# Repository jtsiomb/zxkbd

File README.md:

ZX Spectrum PS/2 keyboard controller
====================================

About
-----
This project is an PS/2 keyboard controller for the ZX Spectrum. It makes it
possible to connect and use an external PS/2 keyboard with the spectrum. It's
based on the a500kbd code: https://github.com/jtsiomb/a500kbd

The PS/2 keyboard controller is built around an AVR atmega168 microcontroller.
The firmware reads PS/2 keyboard scancodes, maintains a virtual spectrum
keyboard state, and monitors the address bus to keep the data lines going into
the ULA continuously up to date with the selected key row state.

NOTE: not done. check back soon.

License
-------
Copyright (C) 2020 John Tsiombikas <nuclear@member.fsf.org>

You are free to use, reproduce, modify, redistribute any parts of this project,
provided you make any derivative work you release, freely available under the
same terms.

More specifically the hardware design is released under the Creative Commons
Attribution Share-Alike license (see `LICENSE.hw` for details), and the
software/firmware is released under the GNU General Public License v3, or later
(see `LICENSE.fw` for details).

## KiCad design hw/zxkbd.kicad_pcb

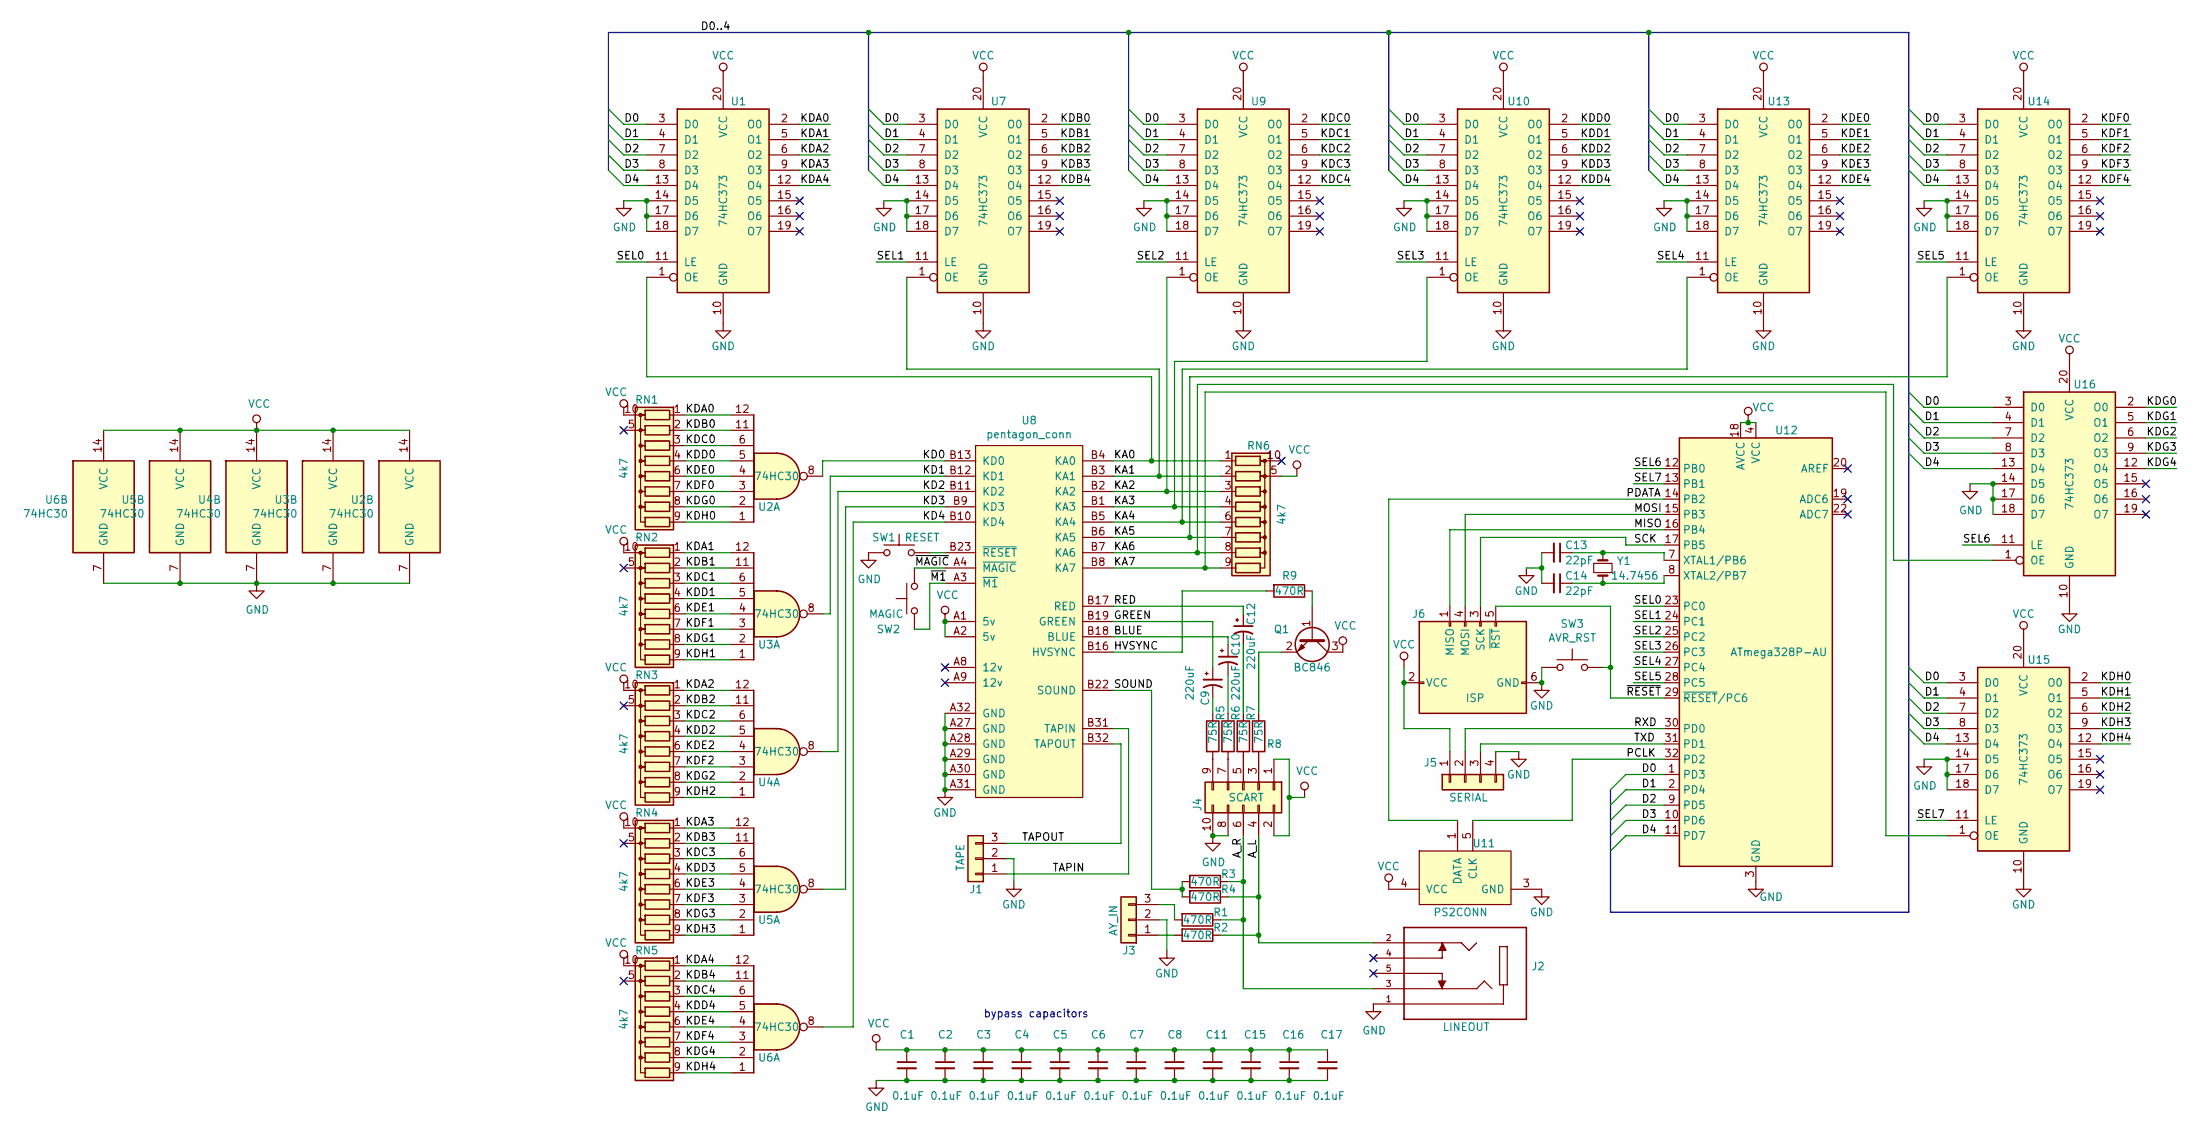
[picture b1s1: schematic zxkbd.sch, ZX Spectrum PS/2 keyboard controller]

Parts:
C1, C2, C3, C4, C5, C6, C7, C8, C11, C15, C16, C17: 0.1uF; C_0805_2012Metric_Pad1.15x1.40mm_HandSolder
C9, C10, C12: 220uF; CP_Elec_6.3x7.7
C13, C14: 22pF; C_0805_2012Metric_Pad1.15x1.40mm_HandSolder
J1: TAPE; PinHeader_1x03_P2.54mm_Vertical
J2: LINEOUT; cui_sj1-3525ng
J3: AY_IN; PinHeader_1x03_P2.54mm_Vertical
J4: SCART; IDC-Header_2x05_P2.54mm_Vertical
J5: SERIAL; PinHeader_1x04_P2.54mm_Vertical
J6: ISP; IDC-Header_2x03_P2.54mm_Vertical
Q1: BC846; SOT-23
R1, R2, R3, R4, R9: 470R; R_0805_2012Metric_Pad1.15x1.40mm_HandSolder
R5, R6, R7, R8: 75R; R_0805_2012Metric_Pad1.15x1.40mm_HandSolder
RN1, RN2, RN3, RN4, RN5, RN6: 4k7; R_Array_Convex_5x1206
SW1: RESET; SW_Push_1P1T_NO_6x6mm_H9.5mm
SW2: MAGIC; SW_Push_1P1T_NO_6x6mm_H9.5mm
SW3: AVR_RST; SW_Push_1P1T_NO_6x6mm_H9.5mm
U1, U7, U9, U10, U13, U14, U15, U16: 74HC373; SOIC-20W_7.5x12.8mm_P1.27mm
U2, U3, U4, U5, U6: 74HC30; SOIC-14_3.9x8.7mm_P1.27mm
U8: pentagon_conn; pentconn
U11: PS2CONN; ps2conn
U12: ATmega328P-AU; TQFP-32_7x7mm_P0.8mm
Y1: 14.7456; Crystal_SMD_ECS_CSM3X-2Pin_7.6x4.1mm

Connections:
/A_L: J2.2, J4.4, R2.1, R4.1
/A_R: J2.3, J4.6, R1.1, R3.1
/BLUE: C10.1, U8.B18 (BLUE)
/D0: U1.3 (D0), U7.3 (D0), U9.3 (D0), U10.3 (D0), U12.1 (PD3), U13.3 (D0), U14.3 (D0), U15.3 (D0), U16.3 (D0)
/D1: U1.4 (D1), U7.4 (D1), U9.4 (D1), U10.4 (D1), U12.2 (PD4), U13.4 (D1), U14.4 (D1), U15.4 (D1), U16.4 (D1)
/D2: U1.7 (D2), U7.7 (D2), U9.7 (D2), U10.7 (D2), U12.9 (PD5), U13.7 (D2), U14.7 (D2), U15.7 (D2), U16.7 (D2)
/D3: U1.8 (D3), U7.8 (D3), U9.8 (D3), U10.8 (D3), U12.10 (PD6), U13.8 (D3), U14.8 (D3), U15.8 (D3), U16.8 (D3)
/D4: U1.13 (D4), U7.13 (D4), U9.13 (D4), U10.13 (D4), U12.11 (PD7), U13.13 (D4), U14.13 (D4), U15.13 (D4), U16.13 (D4)
/GREEN: C9.1, U8.B19 (GREEN)
/HVSYNC: R9.2, U8.B16 (HVSYNC)
/KA0: RN6.1 (R1), U1.1 (OE), U8.B4 (KA0)
/KA1: RN6.2 (R2), U7.1 (OE), U8.B3 (KA1)
/KA2: RN6.3 (R3), U8.B2 (KA2), U9.1 (OE)
/KA3: RN6.4 (R4), U8.B1 (KA3), U10.1 (OE)
/KA4: RN6.6 (R6), U8.B5 (KA4), U13.1 (OE)
/KA5: RN6.7 (R7), U8.B6 (KA5), U14.1 (OE)
/KA6: RN6.8 (R8), U8.B7 (KA6), U16.1 (OE)
/KA7: RN6.9 (R9), U8.B8 (KA7), U15.1 (OE)
/KD0: U2.8, U8.B13 (KD0)
/KD1: U3.8, U8.B12 (KD1)
/KD2: U4.8, U8.B11 (KD2)
/KD3: U5.8, U8.B9 (KD3)
/KD4: U6.8, U8.B10 (KD4)
/KDA0: RN1.1 (R1), U1.2 (O0), U2.12
/KDA1: RN2.1 (R1), U1.5 (O1), U3.12
/KDA2: RN3.1 (R1), U1.6 (O2), U4.12
/KDA3: RN4.1 (R1), U1.9 (O3), U5.12
/KDA4: RN5.1 (R1), U1.12 (O4), U6.12
/KDB0: RN1.2 (R2), U2.11, U7.2 (O0)
/KDB1: RN2.2 (R2), U3.11, U7.5 (O1)
/KDB2: RN3.2 (R2), U4.11, U7.6 (O2)
/KDB3: RN4.2 (R2), U5.11, U7.9 (O3)
/KDB4: RN5.2 (R2), U6.11, U7.12 (O4)
/KDC0: RN1.3 (R3), U2.6, U9.2 (O0)
/KDC1: RN2.3 (R3), U3.6, U9.5 (O1)
/KDC2: RN3.3 (R3), U4.6, U9.6 (O2)
/KDC3: RN4.3 (R3), U5.6, U9.9 (O3)
/KDC4: RN5.3 (R3), U6.6, U9.12 (O4)
/KDD0: RN1.4 (R4), U2.5, U10.2 (O0)
/KDD1: RN2.4 (R4), U3.5, U10.5 (O1)
/KDD2: RN3.4 (R4), U4.5, U10.6 (O2)
/KDD3: RN4.4 (R4), U5.5, U10.9 (O3)
/KDD4: RN5.4 (R4), U6.5, U10.12 (O4)
/KDE0: RN1.6 (R6), U2.4, U13.2 (O0)
/KDE1: RN2.6 (R6), U3.4, U13.5 (O1)
/KDE2: RN3.6 (R6), U4.4, U13.6 (O2)
/KDE3: RN4.6 (R6), U5.4, U13.9 (O3)
/KDE4: RN5.6 (R6), U6.4, U13.12 (O4)
/KDF0: RN1.7 (R7), U2.3, U14.2 (O0)
/KDF1: RN2.7 (R7), U3.3, U14.5 (O1)
/KDF2: RN3.7 (R7), U4.3, U14.6 (O2)
/KDF3: RN4.7 (R7), U5.3, U14.9 (O3)
/KDF4: RN5.7 (R7), U6.3, U14.12 (O4)
/KDG0: RN1.8 (R8), U2.2, U16.2 (O0)
/KDG1: RN2.8 (R8), U3.2, U16.5 (O1)
/KDG2: RN3.8 (R8), U4.2, U16.6 (O2)
/KDG3: RN4.8 (R8), U5.2, U16.9 (O3)
/KDG4: RN5.8 (R8), U6.2, U16.12 (O4)
/KDH0: RN1.9 (R9), U2.1, U15.2 (O0)
/KDH1: RN2.9 (R9), U3.1, U15.5 (O1)
/KDH2: RN3.9 (R9), U4.1, U15.6 (O2)
/KDH3: RN4.9 (R9), U5.1, U15.9 (O3)
/KDH4: RN5.9 (R9), U6.1, U15.12 (O4)
/MISO: J6.1 (MISO), U12.16 (PB4)
/MOSI: J6.4 (MOSI), U12.15 (PB3)
/PCLK: U11.5 (CLK), U12.32 (PD2)
/PDATA: U11.1 (DATA), U12.14 (PB2)
/RED: C12.1, U8.B17 (RED)
/RXD: J5.2, U12.30 (PD0)
/SCK: J6.3 (SCK), U12.17 (PB5)
/SEL0: U1.11 (LE), U12.23 (PC0)
/SEL1: U7.11 (LE), U12.24 (PC1)
/SEL2: U9.11 (LE), U12.25 (PC2)
/SEL3: U10.11 (LE), U12.26 (PC3)
/SEL4: U12.27 (PC4), U13.11 (LE)
/SEL5: U12.28 (PC5), U14.11 (LE)
/SEL6: U12.12 (PB0), U16.11 (LE)
/SEL7: U12.13 (PB1), U15.11 (LE)
/SOUND: R3.2, R4.2, U8.B22 (SOUND)
/TAPIN: J1.1, U8.B31 (TAPIN)
/TAPOUT: J1.3, U8.B32 (TAPOUT)
/TXD: J5.3, U12.31 (PD1)
/~M1: SW2.1, U8.A3 (~M1)
/~MAGIC: SW2.2, U8.A4 (~MAGIC)
/~RESET: J6.5 (~RST), SW3.2, U12.29 (~RESET~/PC6)
GND: C1.2, C2.2, C3.2, C4.2, C5.2, C6.2, C7.2, C8.2, C11.2, C13.2, C14.2, C15.2, C16.2, C17.2, J1.2, J2.1, J3.2, J4.8, J4.10, J5.4, J6.6 (GND), SW1.1, SW3.1, U1.10 (GND), U1.14 (D5), U1.17 (D6), U1.18 (D7), U2.7 (GND), U3.7 (GND), U4.7 (GND), U5.7 (GND), U6.7 (GND), U7.10 (GND), U7.14 (D5), U7.17 (D6), U7.18 (D7), U8.A27 (GND), U8.A28 (GND), U8.A29 (GND), U8.A30 (GND), U8.A31 (GND), U8.A32 (GND), U9.10 (GND), U9.14 (D5), U9.17 (D6), U9.18 (D7), U10.10 (GND), U10.14 (D5), U10.17 (D6), U10.18 (D7), U11.3 (GND), U12.3 (GND), U12.5 (GND), U12.21 (GND), U13.10 (GND), U13.14 (D5), U13.17 (D6), U13.18 (D7), U14.10 (GND), U14.14 (D5), U14.17 (D6), U14.18 (D7), U15.10 (GND), U15.14 (D5), U15.17 (D6), U15.18 (D7), U16.10 (GND), U16.14 (D5), U16.17 (D6), U16.18 (D7)
unnamed: C9.2, R5.1
unnamed: C10.2, R6.1
unnamed: C12.2, R7.1
unnamed: C13.1, U12.7 (XTAL1/PB6), Y1.1
unnamed: C14.1, U12.8 (XTAL2/PB7), Y1.2
unnamed: J3.1, R2.2
unnamed: J3.3, R1.2
unnamed: J4.3, R8.2
unnamed: J4.5, R7.2
unnamed: J4.7, R6.2
unnamed: J4.9, R5.2
unnamed: Q1.1 (B), R9.1
unnamed: Q1.2 (E), R8.1
unnamed: SW1.2, U8.B23 (~RESET)
VCC: C1.1, C2.1, C3.1, C4.1, C5.1, C6.1, C7.1, C8.1, C11.1, C15.1, C16.1, C17.1, J4.1, J4.2, J5.1, J6.2 (VCC), Q1.3 (C), RN1.10 (common), RN2.10 (common), RN3.10 (common), RN4.10 (common), RN5.10 (common), RN6.5 (common), U1.20 (VCC), U2.14 (VCC), U3.14 (VCC), U4.14 (VCC), U5.14 (VCC), U6.14 (VCC), U7.20 (VCC), U8.A1 (5v), U8.A2 (5v), U9.20 (VCC), U10.20 (VCC), U11.4 (VCC), U12.4 (VCC), U12.6 (VCC), U12.18 (AVCC), U13.20 (VCC), U14.20 (VCC), U15.20 (VCC), U16.20 (VCC)

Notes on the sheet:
bypass capacitors

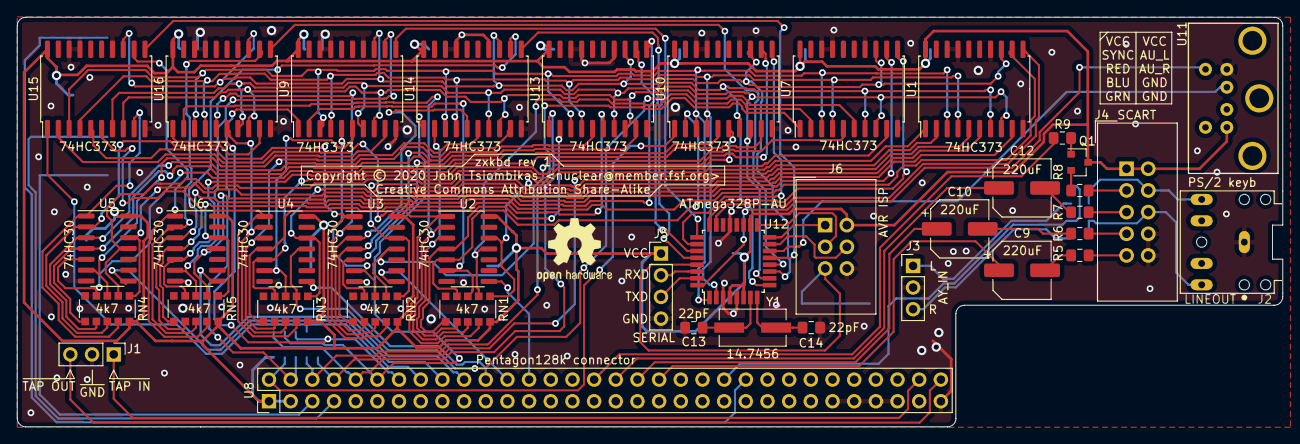
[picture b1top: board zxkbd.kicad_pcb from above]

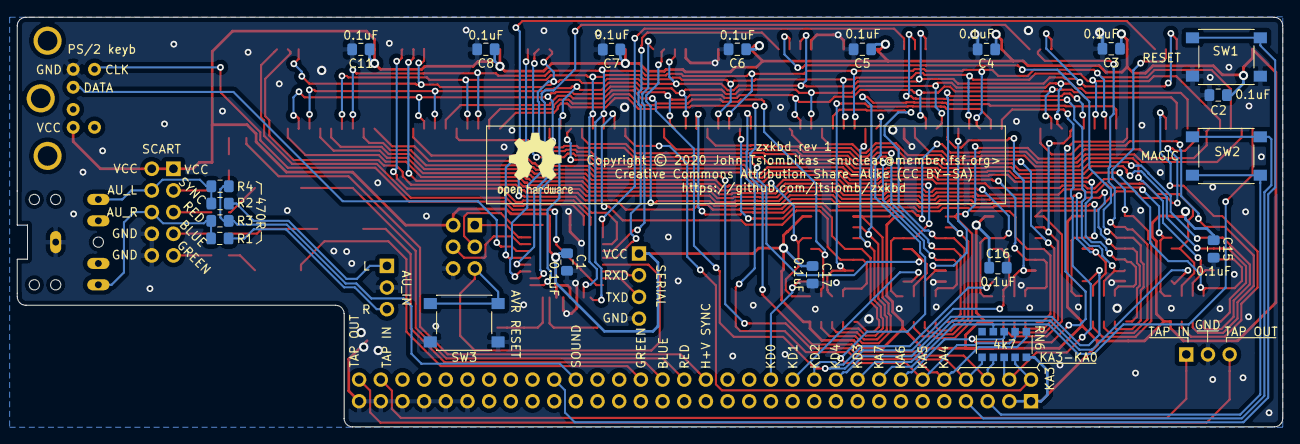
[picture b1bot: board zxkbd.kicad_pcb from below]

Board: 2 copper layers, 148.3 x 48.0 mm, 59 parts (20 on the bottom side), 101 nets.

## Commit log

2020-02-05 added under construction note in the readme
2020-02-10 debugging
2020-02-12 started on the hardware design
2020-02-13 added resistor network symbol
2020-02-15 designing the pcb
2020-02-17 PCB first pass
2020-02-17 via stitching
2020-02-17 fixed PCB mistake, AVR reset switch overlapped with ISP header pins on the back side of the board.
2020-02-18 finishing the pcb
2020-02-18 labels on the pcb
2020-02-18 PCB completed
2020-02-19 added bom
2020-02-19 hacked the firmware to work with the new design. Can't test yet. Hopefully it'll work.
2020-03-19 corrected BOM

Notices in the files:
hw/zxkbd.kicad_pcb:
Copyright © 2020 John Tsiombikas
Creative Commons Attribution Share-Alike (CC BY-SA)
hw/zxkbd.sch:
License: Creative Commons Attribution Share-Alike (CC BY-SA)
